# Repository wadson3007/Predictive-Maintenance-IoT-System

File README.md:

# Predictive Maintenance IoT System for Industrial Motors

A two-node IoT system that monitors industrial motors in real time to predict failures before they happen. A **sensor node** measures temperature and vibration directly on the motor, and sends the data wirelessly to a **gateway** that displays status, triggers alarms, and pushes the readings to the cloud

Built with custom PCBs (KiCad), 3D-printed enclosures (Onshape), and ESP32-S3 microcontrollers

## Why I made it

This project started when I was asked to do an IoT project based on some industrial project, so I developed a basic version of this complete project, I made it on a weekend using only one breadboard and one ESP32 DevKit module

The reason behind the two versions of this project are that on big industrial companies they spend a lot of money on keeping workers near the equipment to be sure that all is working well and my first idea was what would happen if we could cut those additional payments, so I came up with the idea of a project that could monitor the changes on the motors and make an alarm when things are getting bad

Im not saying that it could replace all the workers that are there, because the motors still need someone to operate them but I think this project could cut a little bit of the physical and mental strain on staff

## How it works

The system has two nodes that communicate wirelessly:

### Sensor Node (On the motor)

Mounted directly on the motor, its constantly cheking the two signals that reveal a failure

- **Temperature** a MAX6675 module with a K-type thermocouple reads the motors temperature
- **Vibration** a GY-25 module measures the motors vibration/tilt
- **Threshold** a trimmer potentiometer lets you set the vibration alarm threshold by hand
- **Status LEDs** 4 LEDs show the temperature state at a glance (blue = cold, green = normal, yellow = warning, red = critical)
- **Calibration button** sets the reference "normal" state for the motor being monitored

The sensor node sends its readings to the gateway using **ESP-NOW**, a fast, low-power wireless protocol that doesnt need a WiFi router

### Gateway (Control point)

Placed where an operator can see it, the gateway receives the data and acts on it:

- **OLED display** shows live temperature, vibration, and system status
- **Buzzer** sounds an audible alarm when a reading crosses a dangerous threshold
- **Status LEDs** 3 LEDs indicate WiFi connection, active alarm, and MQTT/cloud status
- **ACK button** lets the operator acknowledge and silence an alarm

The gateway forwards every reading to the cloud over **MQTT**, so the motor data can be logged and monitored remotely

## Pinout

### Sensor Node (ESP32-S3-WROOM-1)

**MAX6675** (temperature):

- SCK: GPIO12
- SO: GPIO13
- CS: GPIO10

**GY-25** (vibration):

- TX: GPIO18
- RX: GPIO17

**Potentiometer** (threshold): 

- GPIO4

**Calibration button**:

- GPIO15

**LEDs**:

- Blue (cold): GPIO8
- Green (normal): GPIO7
- Yellow (warning): GPIO6
- Red (critical): GPIO5

**USB-C**:

- D-: GPIO19
- D+: GPIO20

### Gateway (ESP32-S3-WROOM-1)

**OLED display** (I2C):

- SDA: GPIO8
- SCL: GPIO9

**Buzzer**:

- GPIO4

**ACK button**:

- GPIO15

**LEDs**:

- WiFi (green): GPIO5
- Alarm (red): GPIO6
- MQTT (blue): GPIO7

**USB-C**:

- D-: GPIO19
- D+: GPIO20

## Screenshots

### Sensor Node

**3D Render**

**PCB Layout**

**Schematic**

### Gateway

**3D Render**

**PCB Layout**

**Schematic**

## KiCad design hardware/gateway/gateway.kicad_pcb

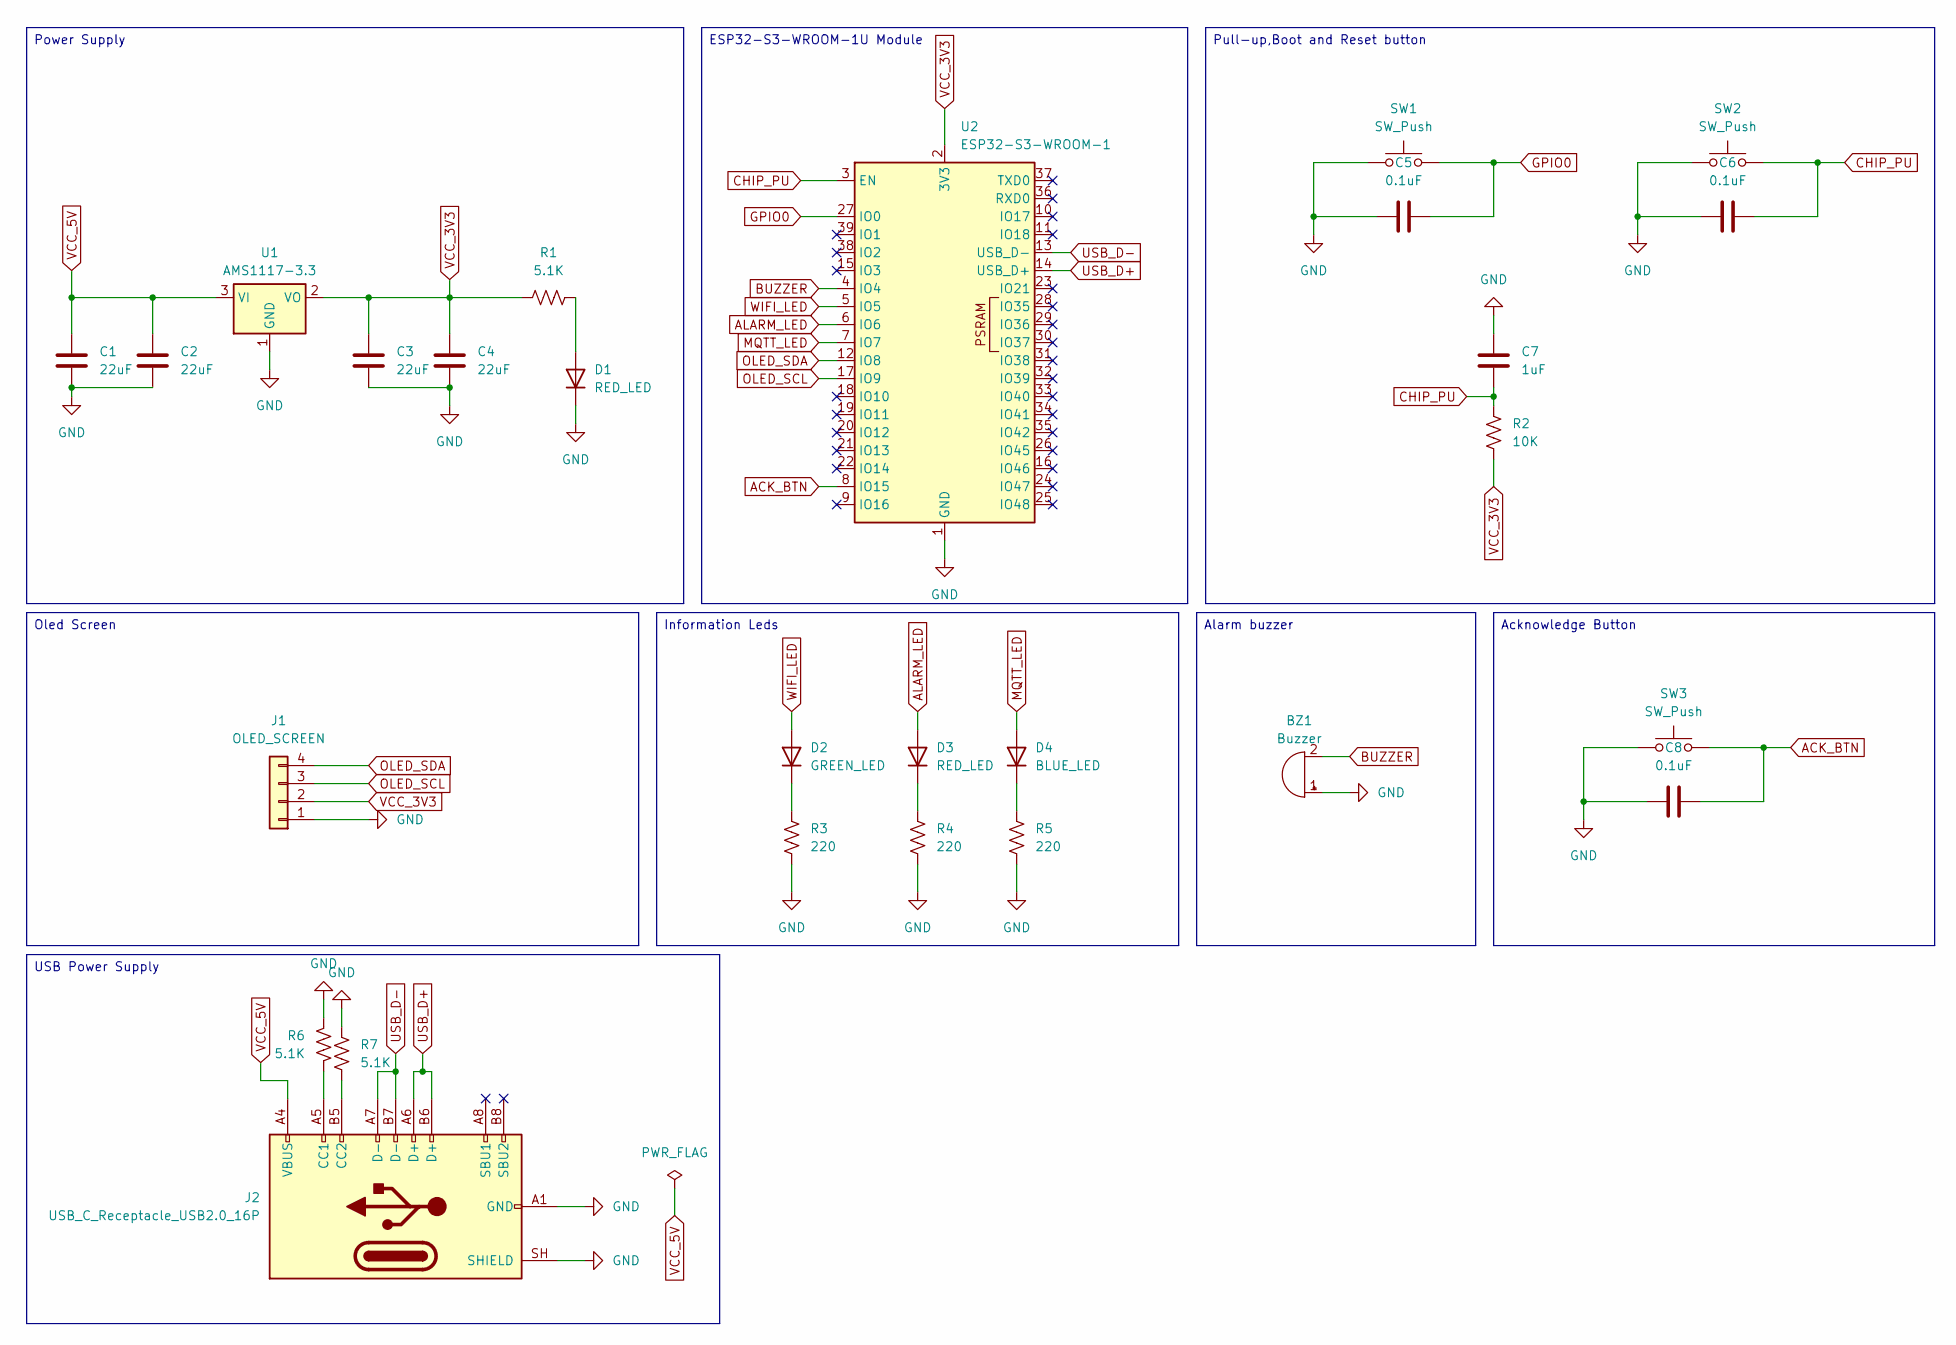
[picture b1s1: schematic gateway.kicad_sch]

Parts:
BZ1: Buzzer; Buzzer_12x9.5RM7.6
C1, C2, C3, C4: 22uF; CP_Radial_D5.0mm_P2.00mm
C5, C6, C8: 0.1uF; C_Disc_D5.0mm_W2.5mm_P5.00mm
C7: 1uF; C_Disc_D5.0mm_W2.5mm_P5.00mm
D1, D3: RED_LED; LED_D5.0mm
D2: GREEN_LED; LED_D5.0mm
D4: BLUE_LED; LED_D5.0mm
J1: OLED_SCREEN; PinHeader_1x04_P2.54mm_Vertical
J2: USB_C_Receptacle_USB2.0_16P; USB_C_Receptacle_XKB_U262-16XN-4BVC11
R1, R6, R7: 5.1K; R_Axial_DIN0207_L6.3mm_D2.5mm_P7.62mm_Horizontal
R2: 10K; R_Axial_DIN0207_L6.3mm_D2.5mm_P7.62mm_Horizontal
R3, R4, R5: 220; R_Axial_DIN0207_L6.3mm_D2.5mm_P7.62mm_Horizontal
SW1, SW2, SW3: SW_Push; SW_PUSH_6mm
U1: AMS1117-3.3; SOT-223-3_TabPin2
U2: ESP32-S3-WROOM-1

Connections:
ACK_BTN: C8.1, SW3.2, U2.8 (IO15)
ALARM_LED: D3.2 (A), U2.6 (IO6)
BUZZER: BZ1.2 (-), U2.4 (IO4)
CHIP_PU: C6.1, C7.2, R2.1, SW2.2, U2.3 (EN)
GND: BZ1.1 (+), C1.2, C2.2, C3.2, C4.2, C5.2, C6.2, C7.1, C8.2, D1.1 (K), J1.1, J2.A1 (GND), J2.A12 (GND), J2.B1 (GND), J2.B12 (GND), J2.SH (SHIELD), R3.2, R4.2, R5.2, R6.1, R7.1, SW1.1, SW2.1, SW3.1, U1.1 (GND), U2.1 (GND), U2.40 (GND), U2.41 (GND)
GPIO0: C5.1, SW1.2, U2.27 (IO0)
MQTT_LED: D4.2 (A), U2.7 (IO7)
unnamed: D1.2 (A), R1.2
unnamed: D2.1 (K), R3.1
unnamed: D3.1 (K), R4.1
unnamed: D4.1 (K), R5.1
unnamed: J2.A5 (CC1), R6.2
unnamed: J2.B5 (CC2), R7.2
OLED_SCL: J1.3, U2.17 (IO9)
OLED_SDA: J1.4, U2.12 (IO8)
USB_D+: J2.A6 (D+), J2.B6 (D+), U2.14 (USB_D+)
USB_D-: J2.A7 (D-), J2.B7 (D-), U2.13 (USB_D-)
VCC_3V3: C3.1, C4.1, J1.2, R1.1, R2.2, U1.2 (VO), U2.2 (3V3)
VCC_5V: C1.1, C2.1, J2.A4 (VBUS), J2.A9 (VBUS), J2.B4 (VBUS), J2.B9 (VBUS), U1.3 (VI)
WIFI_LED: D2.2 (A), U2.5 (IO5)

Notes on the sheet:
Alarm buzzer
Acknowledge Button
Pull-up,Boot and Reset button
ESP32-S3-WROOM-1U Module
Information Leds
USB Power Supply
Oled Screen
Power Supply

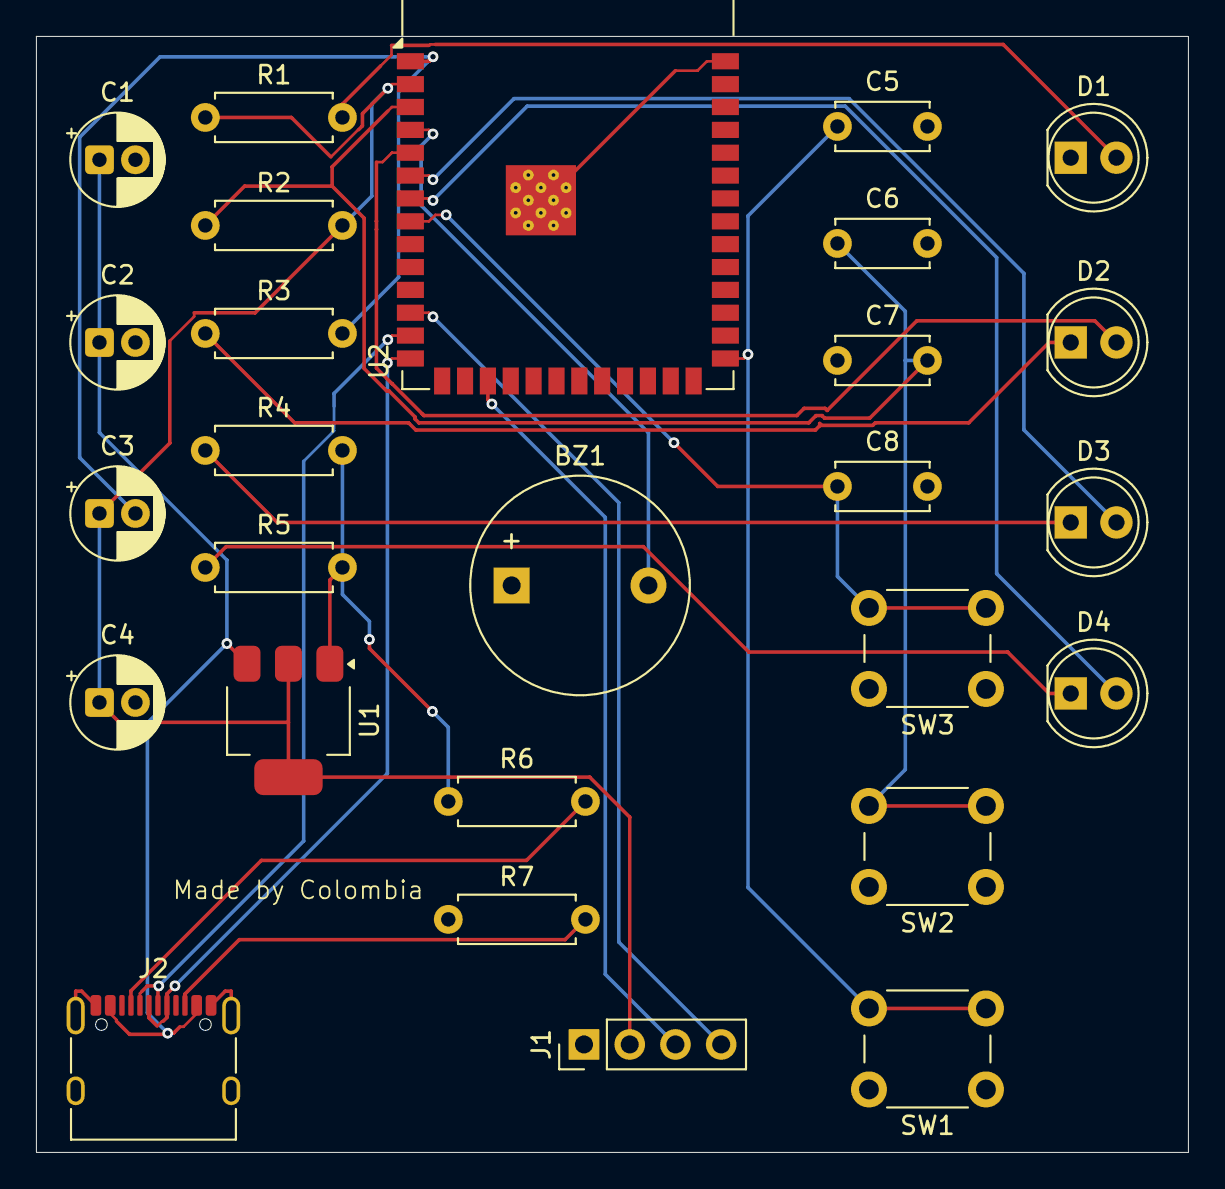
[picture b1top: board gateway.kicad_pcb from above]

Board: 2 copper layers, 64.0 x 62.0 mm, 27 parts (0 on the bottom side), 20 nets.

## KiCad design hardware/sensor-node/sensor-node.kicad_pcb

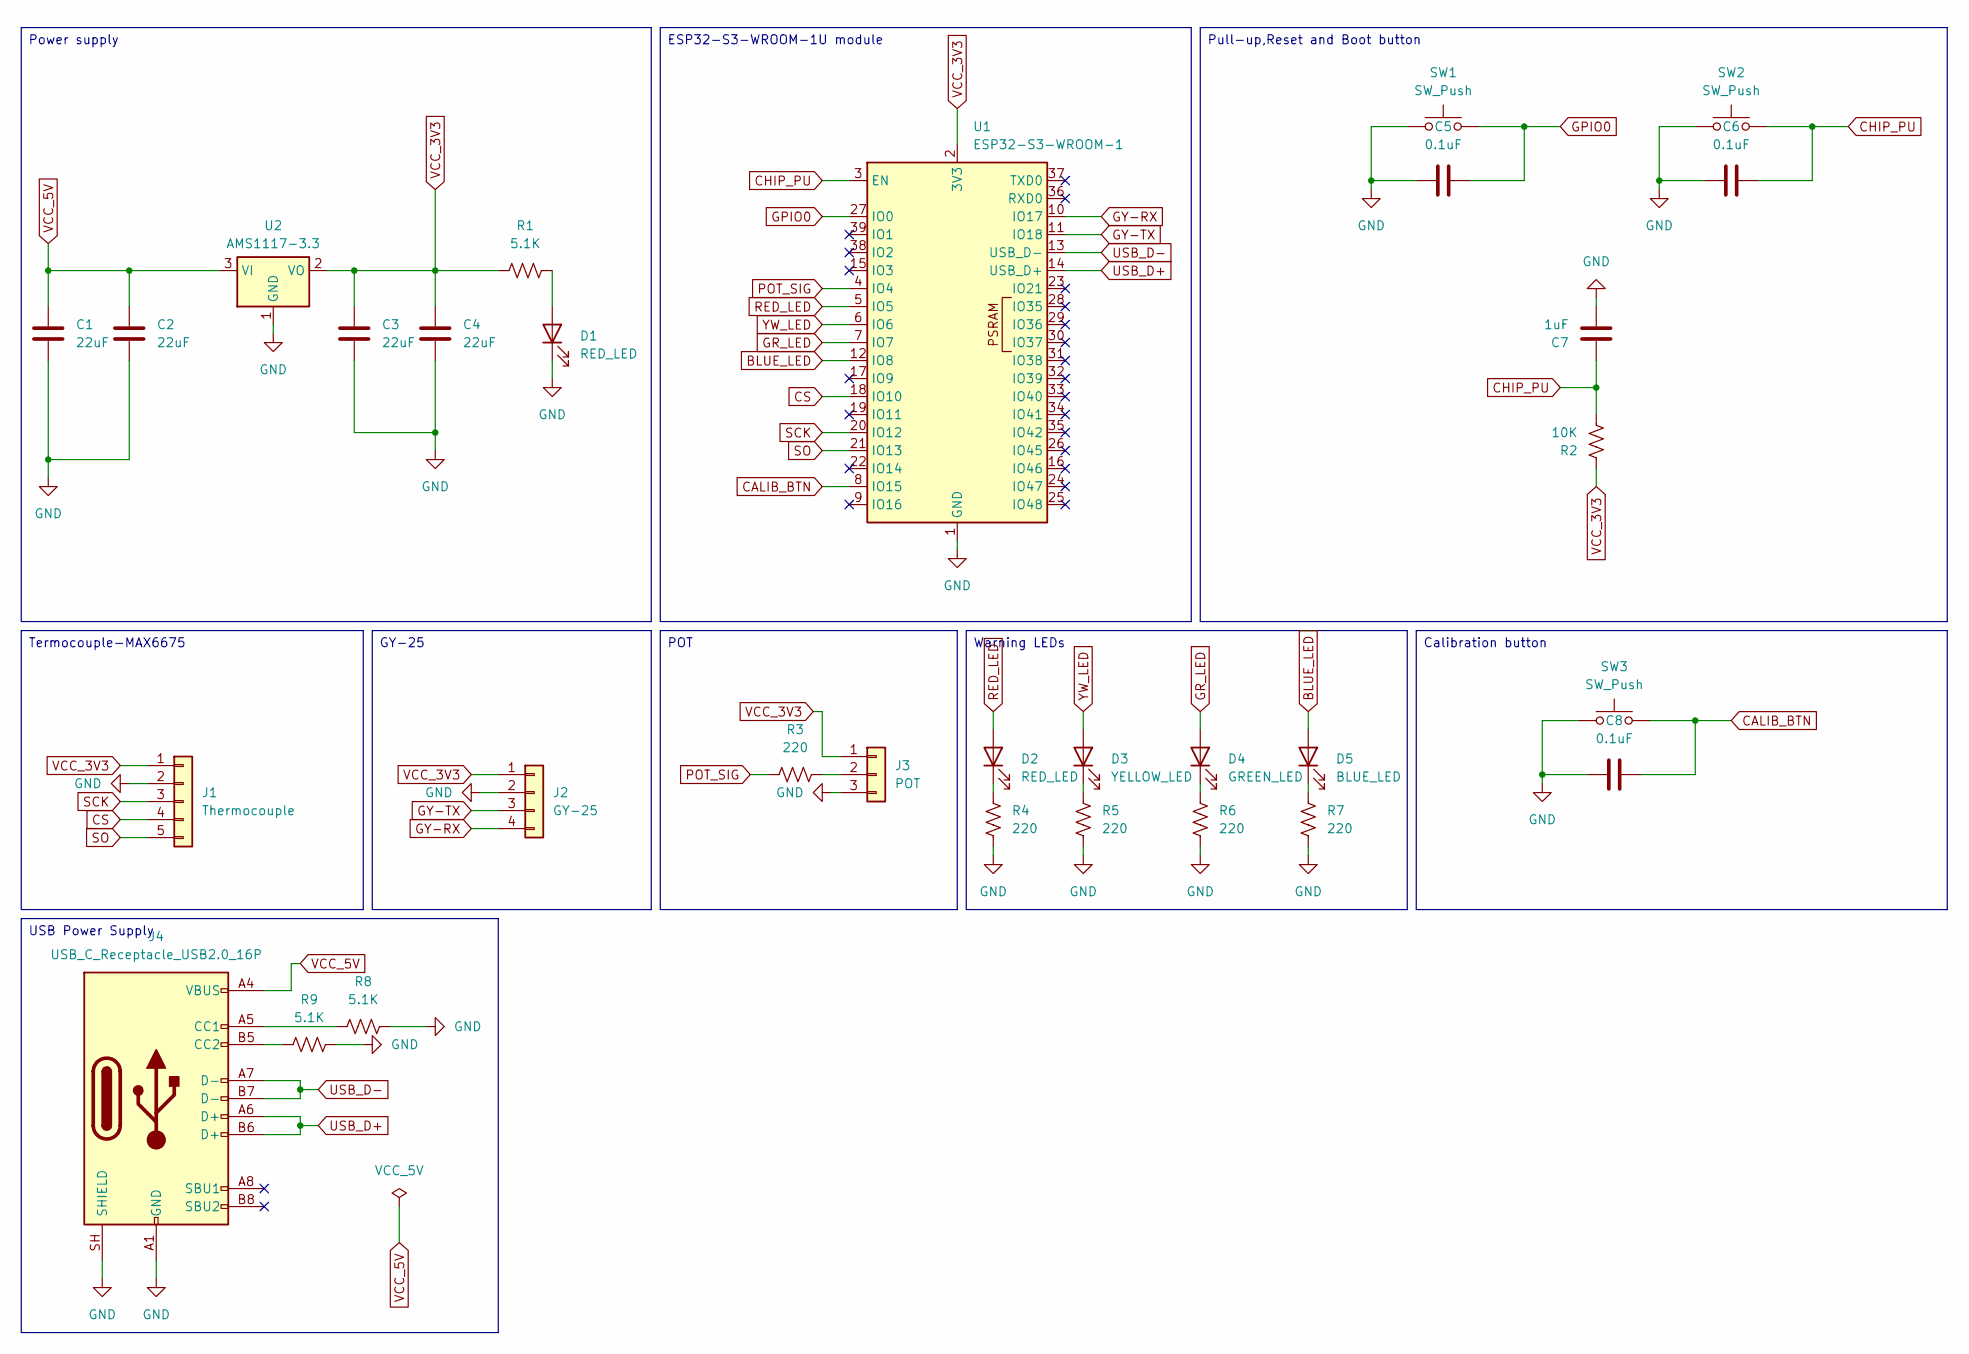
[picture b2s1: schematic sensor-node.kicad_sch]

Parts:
C1, C2, C3, C4: 22uF; CP_Radial_D5.0mm_P2.00mm
C5, C6, C8: 0.1uF; C_Disc_D5.0mm_W2.5mm_P5.00mm
C7: 1uF; CP_Radial_D5.0mm_P2.00mm
D1, D2: RED_LED; LED_D5.0mm
D3: YELLOW_LED; LED_D5.0mm
D4: GREEN_LED; LED_D5.0mm
D5: BLUE_LED; LED_D5.0mm
J1: Thermocouple; PinHeader_1x05_P2.54mm_Vertical
J2: GY-25; PinHeader_1x04_P2.54mm_Vertical
J3: POT; PinHeader_1x03_P2.54mm_Vertical
J4: USB_C_Receptacle_USB2.0_16P; USB_C_Receptacle_XKB_U262-16XN-4BVC11
R1, R8, R9: 5.1K; R_Axial_DIN0207_L6.3mm_D2.5mm_P7.62mm_Horizontal
R2: 10K; R_Axial_DIN0207_L6.3mm_D2.5mm_P7.62mm_Horizontal
R3, R4, R5, R6, R7: 220; R_Axial_DIN0207_L6.3mm_D2.5mm_P7.62mm_Horizontal
SW1, SW2, SW3: SW_Push; SW_PUSH_6mm
U1: ESP32-S3-WROOM-1
U2: AMS1117-3.3; SOT-223-3_TabPin2

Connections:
BLUE_LED: D5.2 (A), U1.12 (IO8)
CALIB_BTN: C8.2, SW3.2, U1.8 (IO15)
CHIP_PU: C6.2, C7.1, R2.1, SW2.2, U1.3 (EN)
CS: J1.4, U1.18 (IO10)
GND: C1.2, C2.2, C3.2, C4.2, C5.1, C6.1, C7.2, C8.1, D1.1 (K), J1.2, J2.2, J3.3, J4.A1 (GND), J4.A12 (GND), J4.B1 (GND), J4.B12 (GND), J4.SH (SHIELD), R4.1, R5.1, R6.1, R7.1, R8.2, R9.2, SW1.1, SW2.1, SW3.1, U1.1 (GND), U1.40 (GND), U1.41 (GND), U2.1 (GND)
GPIO0: C5.2, SW1.2, U1.27 (IO0)
GR_LED: D4.2 (A), U1.7 (IO7)
GY-RX: J2.4, U1.10 (IO17)
GY-TX: J2.3, U1.11 (IO18)
unnamed: D1.2 (A), R1.1
unnamed: D2.1 (K), R4.2
unnamed: D3.1 (K), R5.2
unnamed: D4.1 (K), R6.2
unnamed: D5.1 (K), R7.2
unnamed: J3.2, R3.1
unnamed: J4.A5 (CC1), R8.1
unnamed: J4.B5 (CC2), R9.1
POT_SIG: R3.2, U1.4 (IO4)
RED_LED: D2.2 (A), U1.5 (IO5)
SCK: J1.3, U1.20 (IO12)
SO: J1.5, U1.21 (IO13)
USB_D+: J4.A6 (D+), J4.B6 (D+), U1.14 (USB_D+)
USB_D-: J4.A7 (D-), J4.B7 (D-), U1.13 (USB_D-)
VCC_3V3: C3.1, C4.1, J1.1, J2.1, J3.1, R1.2, R2.2, U1.2 (3V3), U2.2 (VO)
VCC_5V: C1.1, C2.1, J4.A4 (VBUS), J4.A9 (VBUS), J4.B4 (VBUS), J4.B9 (VBUS), U2.3 (VI)
YW_LED: D3.2 (A), U1.6 (IO6)

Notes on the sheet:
POT
Warning LEDs
Termocouple-MAX6675
Pull-up,Reset and Boot button
Power supply
Calibration button
ESP32-S3-WROOM-1U module
USB Power Supply
GY-25

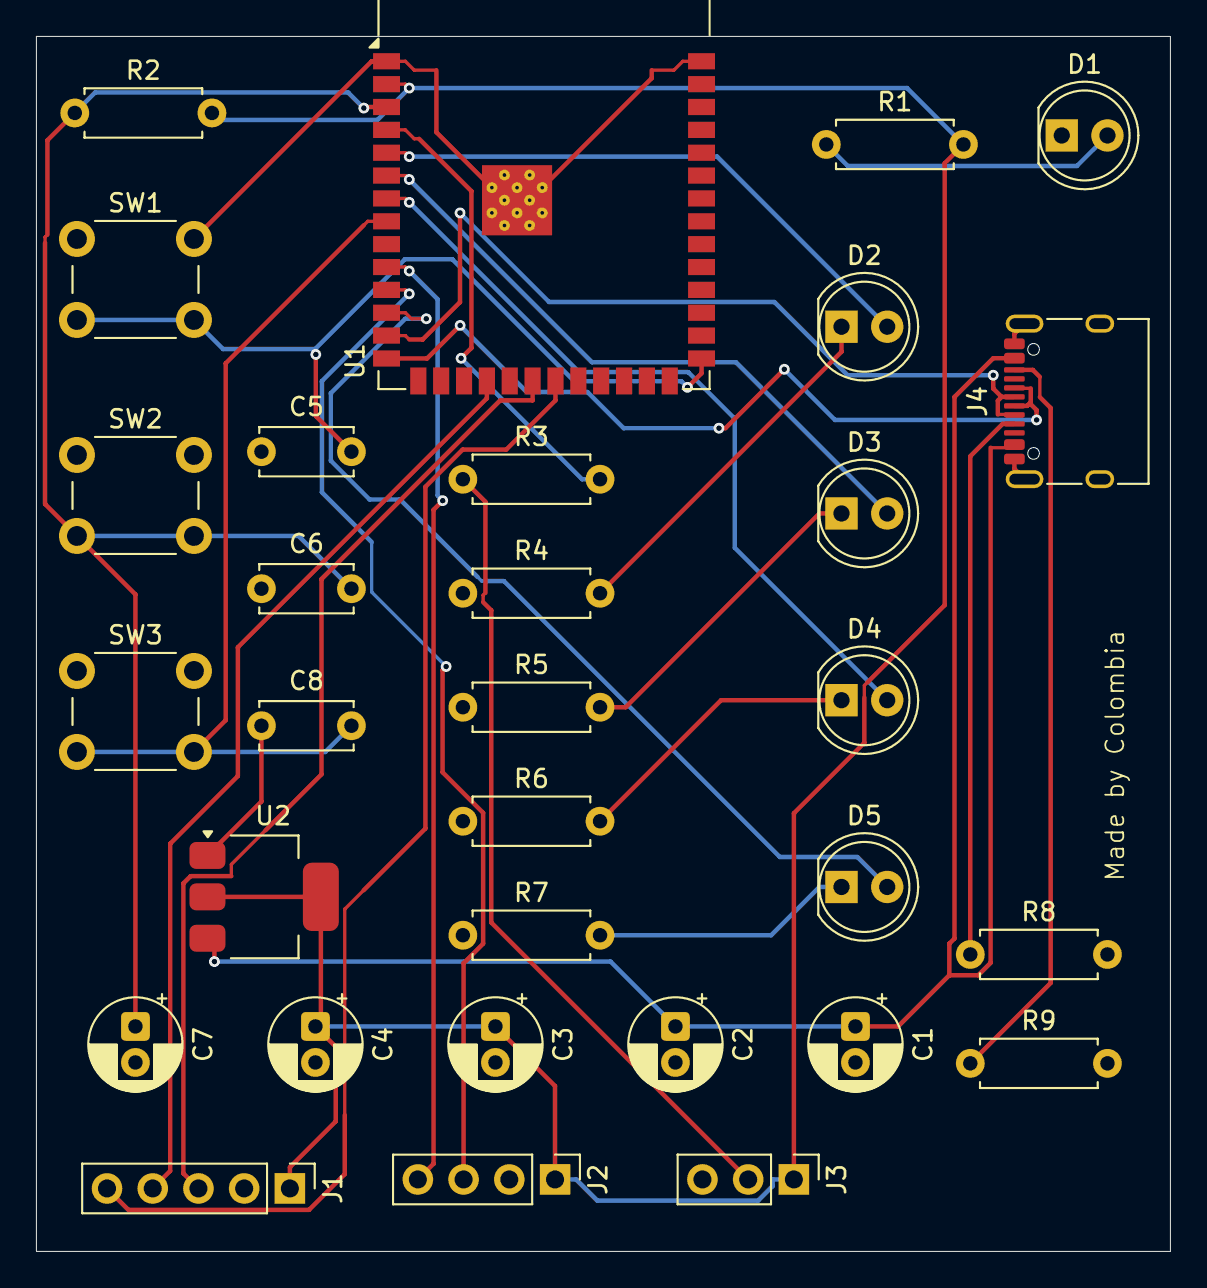
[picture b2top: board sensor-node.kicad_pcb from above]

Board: 2 copper layers, 63.0 x 67.5 mm, 31 parts (0 on the bottom side), 26 nets.

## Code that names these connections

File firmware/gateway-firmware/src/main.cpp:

#include <Arduino.h>
#include <Adafruit_GFX.h>
#include <Adafruit_SSD1306.h>
#include <Wire.h>
#include <WiFi.h>
#include <esp_now.h>
#include <PubSubClient.h>
#include "secrets.h"

#define BUZZER 4
#define WIFI_LED 5
#define ALARM_LED 6
#define MQTT_LED 7
#define OLED_SDA 8
#define OLED_SCL 9
#define ACK_BUTTON 15
#define MQTT_SERVER "io.adafruit.com"
#define MQTT_PORT 1883

struct SensorData
{
  float temperature;
  float vibration;
  float threshold;
  bool alarm;
};

Adafruit_SSD1306 display(128, 64, &Wire, -1);

SensorData received;


WiFiClient espClient;
PubSubClient mqtt(espClient);

void OnDataRecv(const esp_now_recv_info_t *info, const uint8_t *incomingData, int len)
{
  memcpy(&received, incomingData, sizeof(received));
}

void connectMQTT()
{
  while (!mqtt.connected())
  {
    Serial.print("Connecting to MQTT...");
    if (mqtt.connect("gateway-esp32", AIO_USERNAME, AIO_KEY))
    {
      Serial.println("connected");
      digitalWrite(MQTT_LED, HIGH);
    }
    else
    {
      Serial.print("failed, rc=");
      Serial.println(mqtt.state());
      delay(2000);
    }
  }
}

unsigned long lastBeep = 0;
const unsigned long beepInterval = 500;
bool beepOn = false;

bool acknowledged = false;

unsigned long lastDisplay = 0;
const unsigned long displayInterval = 500;

unsigned long lastPublish = 0;
const unsigned long publishInterval = 10000;

void setup()
{
  Serial.begin(115200);
  pinMode(BUZZER, OUTPUT);
  pinMode(WIFI_LED, OUTPUT);
  pinMode(ALARM_LED, OUTPUT);
  pinMode(MQTT_LED, OUTPUT);
  pinMode(ACK_BUTTON, INPUT_PULLUP);

  Wire.begin(OLED_SDA, OLED_SCL);
  display.begin(SSD1306_SWITCHCAPVCC, 0x3C);

  display.clearDisplay();
  display.setTextSize(1);
  display.setTextColor(SSD1306_WHITE);
  display.setCursor(0, 0);
  display.println("Predictive Maintenance");
  display.display();

  WiFi.mode(WIFI_STA);

  WiFi.begin(WIFI_SSID, WIFI_PASSWORD);

  while (WiFi.status() != WL_CONNECTED)
  {
    delay(500);
    Serial.print(".");
  }

  digitalWrite(WIFI_LED, HIGH);
  Serial.println("WiFi connected");

  mqtt.setServer(MQTT_SERVER, MQTT_PORT);

  connectMQTT();

  if (esp_now_init() != ESP_OK)
  {
    Serial.println("Error initializing ESP-NOW");
    return;
  }
  esp_now_register_recv_cb(OnDataRecv);
}

void loop()
{
  if (!mqtt.connected()) {
  connectMQTT();
}
mqtt.loop();

  if (received.alarm)
  {

    if (digitalRead(ACK_BUTTON) == LOW)
    {
      acknowledged = true;
    }

    if (!acknowledged)
    {
      if (millis() - lastBeep >= beepInterval)
      {
        lastBeep = millis();
        beepOn = !beepOn;
        if (beepOn)
        {
          tone(BUZZER, 2000);
          digitalWrite(ALARM_LED, HIGH);
        }
        else
        {
          noTone(BUZZER);
          digitalWrite(ALARM_LED, LOW);
        }
      }
    }
    else
    {
      noTone(BUZZER);
      digitalWrite(ALARM_LED, HIGH);
    }
  }
  else
  {
    digitalWrite(ALARM_LED, LOW);
    noTone(BUZZER);
    acknowledged = false;
  }

  if (millis() - lastDisplay >= displayInterval)
  {
    lastDisplay = millis();

    display.clearDisplay();
    display.setCursor(0, 0);

    display.println("Predictive Maintenance");

    display.print("Temp: ");
    display.print(received.temperature);
    display.println(" C");

    display.print("Vibration: ");
    display.println(received.vibration);

    if (received.alarm)
    {
      display.println("ALARM!");
    }
    else
    {
      display.println("OK");
    }
    display.display();
  }

  if (millis() - lastPublish >= publishInterval) {
    lastPublish = millis();

  char tempStr[10];
  snprintf(tempStr, sizeof(tempStr), "%.2f", received.temperature);
  mqtt.publish(AIO_USERNAME "/feeds/temperature", tempStr);

  char vibStr[10];
  snprintf(vibStr, sizeof(vibStr), "%.2f", received.vibration);
  mqtt.publish(AIO_USERNAME "/feeds/vibration", vibStr);


  char alarmStr[4];
  snprintf(alarmStr, sizeof(alarmStr), "%d", received.alarm);
  mqtt.publish(AIO_USERNAME "/feeds/alarm", alarmStr);
  }
}
